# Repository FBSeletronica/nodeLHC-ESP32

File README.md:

## PT-BR

# nodeLHC-ESP32 

LIVE em formato Hands On Construindo o nova versão da placa de desenvolvimento nodeLHC ESP32, com o Pedro Minatel, utilizando a ferramenta Kicad, o módulo escolhido foi o ESP32 um microcontrolador de baixo custo da Espressif.

Em 2015 durante as oficinas de IoT no Hackerspace, criamos uma primeira versão do nodeLHC com o módulo ESP8266. Assim as pessoas aprenderam as diferentes etapas para construção de placa de circuitos impressos, também soldagem dos componentes da placa de desenvolvimento e programação para o módulo.

Descrições e detalhes:
Essa é uma primeira atividade que ao decorrer iremos construir novos projetos no formato aberto e colaborativo aproveitando a placa de desenvolvimento nodeLHC ESP32

- [KiCad](https://kicad-pcb.org/)
- [LHC KiCad Library](https://github.com/lhc/lhc_kicad_library)
- [Minatel KiCad Library](https://github.com/pedrominatel/minatel-kicad-libraries)
- [SparkFun KiCad Library](https://github.com/sparkfun/SparkFun-KiCad-Libraries)

# checklist
- [x] LIVE 1 - Explicação geral e desenho
- [x] LIVE 2 - Revisão esquemático e desenho da PCB parcial

# Próximos passos
- [ ] Lista de pessoas interessadas nos módulos
- [ ] Feedback comunidade
- [ ] LIVE 3 - Finalizar desenho da placa 
- [ ] Validar artes PCB
- [ ] Lista BOM
- [ ] Produção PCB

# Discourse 
Dúvidas? sugestões publicar na issues ou direto no discourse do LHC 

- [28/07/2020 LIVE - Hands On: Construindo o nodeLHC ESP32 com Kicad](https://discourse.lhc.net.br/t/28-07-2020-live-hands-on-construindo-o-nodelhc-esp32-com-kicad/148/2)
- [11/09/2020 LIVE - Hands On: Construindo o nodeLHC ESP32 com Kicad - Parte 02](https://discourse.lhc.net.br/t/11-09-2020-live-hands-on-construindo-o-nodelhc-esp32-com-kicad-parte-02/160)

# Ainda em construção 11/09/2020

# Log
- 19/08/2020 - Criado o evento, repositório, publicações nas redes sociais gerado link sobre a atividade.
- 02/09/2020 - Criado, divulgado o segundo evento, atualização de links no repositório.
- 06/10/2020 - Listagem das pessoas que responderam o discourse para receber o módulo ESP32

### Referencias

[ESP32 Datasheet](https://www.espressif.com/sites/default/files/documentation/esp32_datasheet_en.pdf)

[ESP32-WROOM Datasheet](https://www.espressif.com/sites/default/files/documentation/esp32-wroom-32d_esp32-wroom-32u_datasheet_en.pdf)

[ESP32 Design Guidelines](https://www.espressif.com/sites/default/files/documentation/esp32_hardware_design_guidelines_en.pdf)

[CH340G](https://cdn.sparkfun.com/datasheets/Dev/Arduino/Other/CH340DS1.PDF)

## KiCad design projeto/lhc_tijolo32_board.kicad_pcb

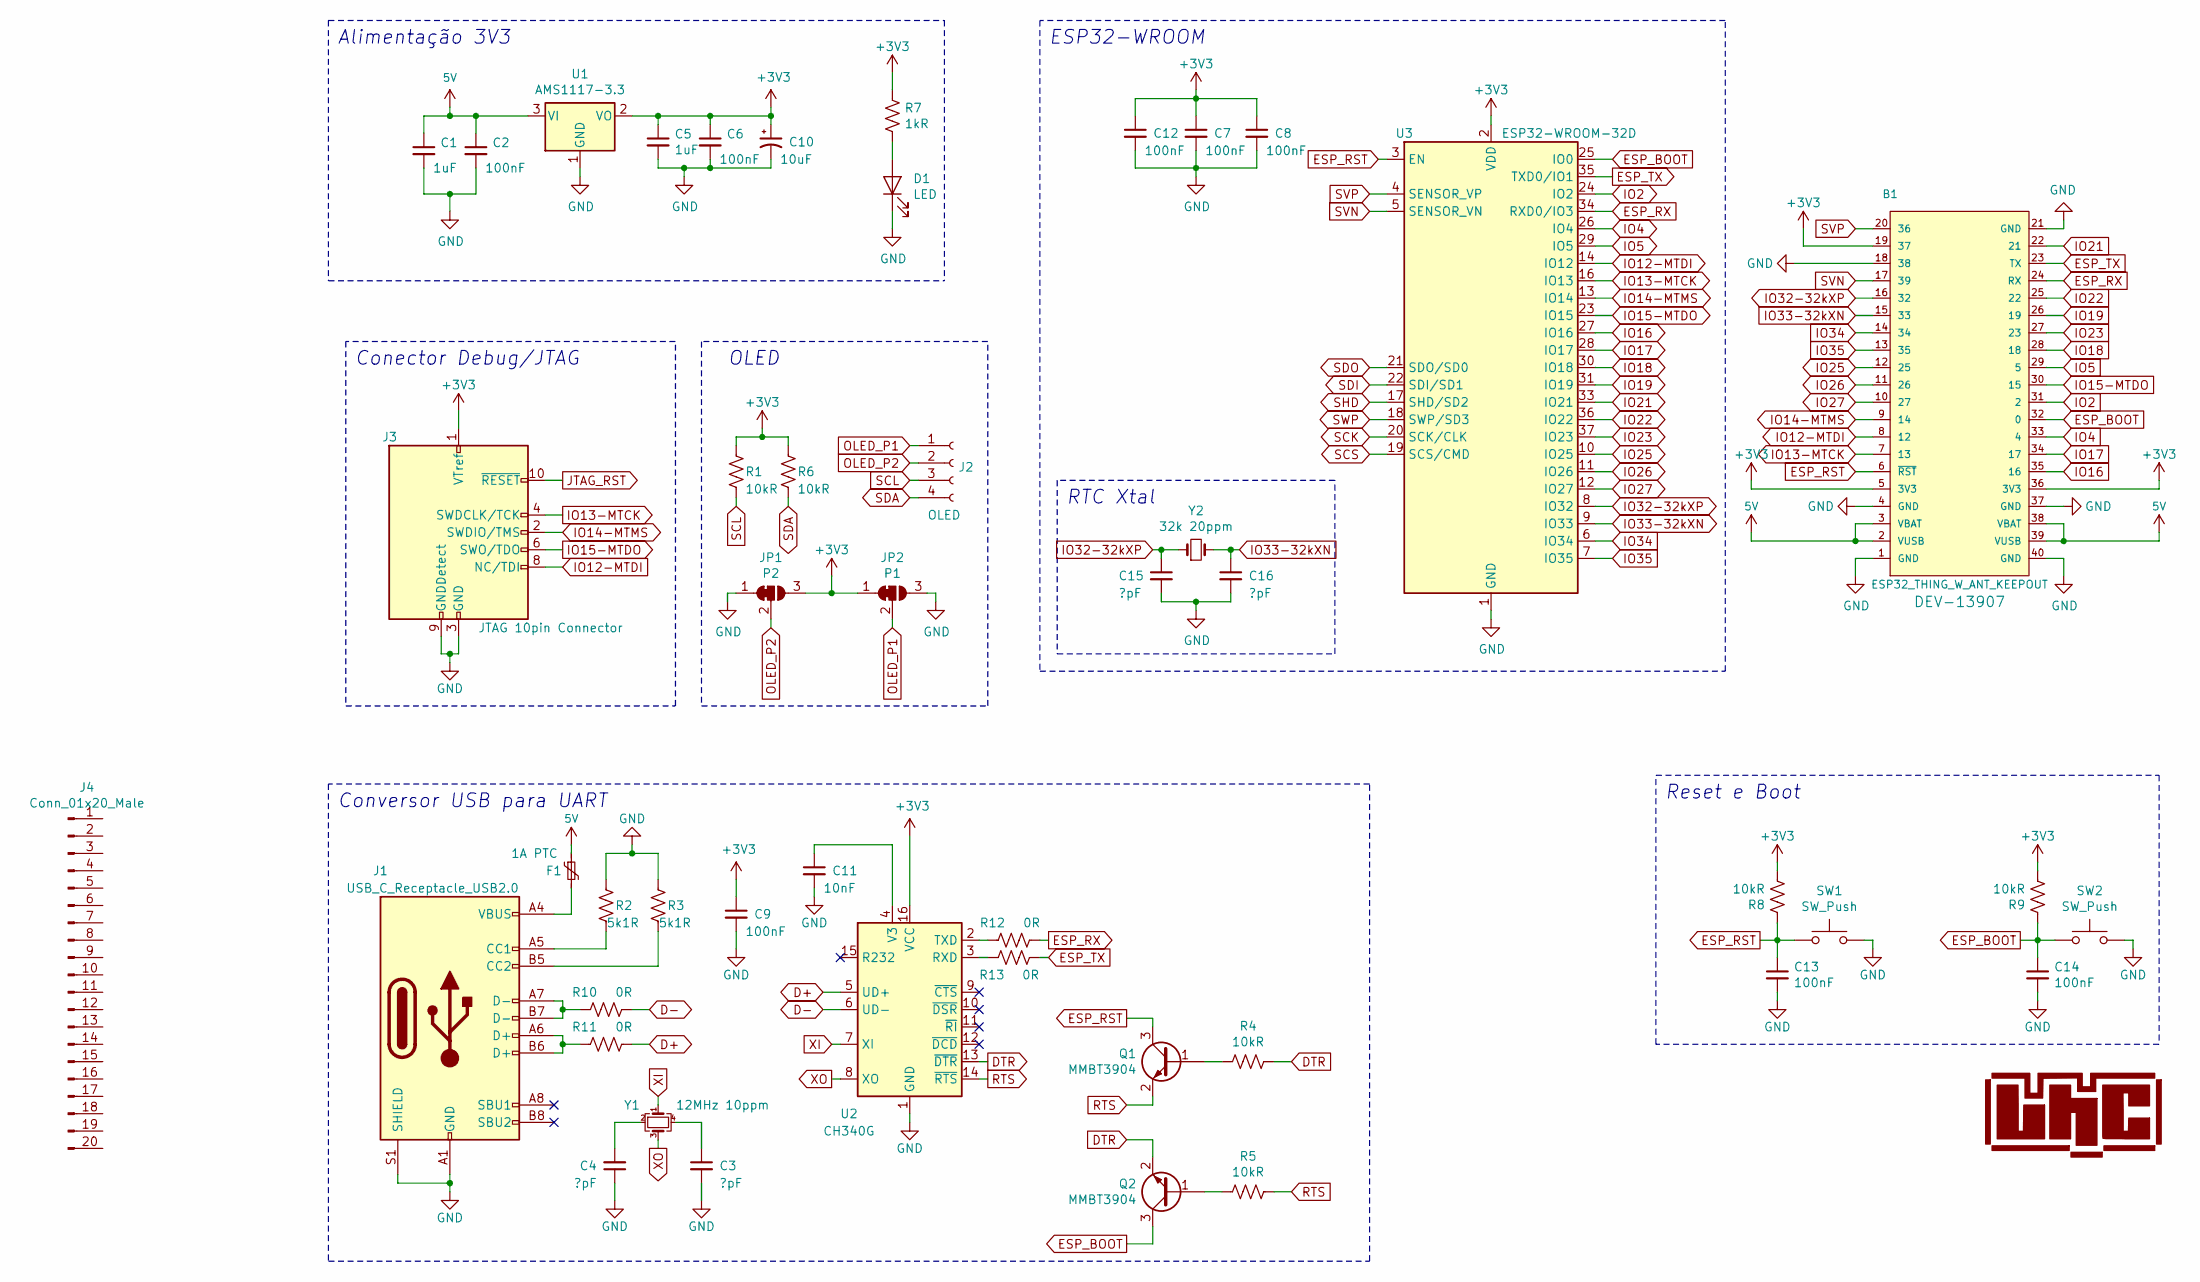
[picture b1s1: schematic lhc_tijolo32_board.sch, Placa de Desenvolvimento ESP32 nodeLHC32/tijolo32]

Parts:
B1: ESP32_THING_W_ANT_KEEPOUT; ESP32_THING
C1, C5: 1uF; C_0603_1608Metric
C2, C6, C7, C8, C9, C12, C13, C14: 100nF; C_0603_1608Metric
C3, C4, C15, C16: ?pF; C_0603_1608Metric
C10: 10uF; CP_EIA-3216-12_Kemet-S; LCSC C7171
C11: 10nF; C_0603_1608Metric
D1: LED; LED_0805_2012Metric
F1: 1A PTC; R_1210_3225Metric
J1: USB_C_Receptacle_USB2.0; USB_C_Receptacle_Palconn_UTC16-G
J2: OLED; PinHeader_1x04_P2.54mm_Vertical
J3: JTAG 10pin Connector; PinHeader_2x05_P1.27mm_Vertical_SMD
J4: Conn_01x20_Male; PinHeader_1x20_P2.54mm_Vertical
JP1: P2; SolderJumper-3_P1.3mm_Bridged12_Pad1.0x1.5mm_NumberLabels
JP2: P1; SolderJumper-3_P1.3mm_Bridged12_Pad1.0x1.5mm_NumberLabels
Q1, Q2: MMBT3904; SOT-23
R1, R4, R5, R6, R8, R9: 10kR; R_0603_1608Metric
R2, R3: 5k1R; R_0603_1608Metric
R7: 1kR; R_0603_1608Metric
R10, R11, R12, R13: 0R; R_0603_1608Metric
SW1, SW2: SW_Push; TACTILE_SWITCH_SMD_6.0X3.5MM
U1: AMS1117-3.3; SOT-223-3_TabPin2; LCSC C6186
U2: CH340G; SOIC-16_3.9x9.9mm_P1.27mm; MPN C14267
U3: ESP32-WROOM-32D; ESP32-WROOM-32
Y1: 12MHz 10ppm; Crystal_SMD_EuroQuartz_MT-4Pin_3.2x2.5mm
Y2: 32k 20ppm; Crystal_SMD_3215-2Pin_3.2x1.5mm

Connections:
5V: B1.2 (VUSB), B1.3 (VBAT), B1.38 (VBAT), B1.39 (VUSB), C1.1, C2.1, F1.1, U1.3 (VI)
+3V3: B1.5 (3V3), B1.19 (37), B1.36 (3V3), C5.1, C6.1, C7.1, C8.1, C9.1, C10.1, C12.1, J3.1 (VTref), JP1.3 (B), JP2.1 (A), R1.1, R6.1, R7.1, R8.2, R9.2, U1.2 (VO), U2.16 (VCC), U3.2 (VDD)
D+: R11.1, U2.5 (UD+)
D-: R10.1, U2.6 (UD-)
DTR: Q2.2 (E), R4.1, U2.13 (~DTR)
ESP_BOOT: B1.32 (0), C14.1, Q2.3 (C), R9.1, SW2.1, U3.25 (IO0)
ESP_RST: B1.6 (~RST~), C13.1, Q1.3 (C), R8.1, SW1.1, U3.3 (EN)
ESP_RX: B1.24 (RX), R12.1, U3.34 (RXD0/IO3)
ESP_TX: B1.23 (TX), R13.2, U3.35 (TXD0/IO1)
GND: B1.1 (GND), B1.4 (GND), B1.18 (38), B1.21 (GND), B1.37 (GND), B1.40 (GND), C1.2, C2.2, C3.2, C4.1, C5.2, C6.2, C7.2, C8.2, C9.2, C10.2, C11.2, C12.2, C13.2, C14.2, C15.2, C16.2, D1.1 (K), J1.A1 (GND), J1.A12 (GND), J1.B1 (GND), J1.B12 (GND), J1.S1 (SHIELD), J3.3 (GND), J3.5 (GND), J3.9 (GNDDetect), JP1.1 (A), JP2.3 (B), R2.1, R3.1, SW1.2, SW2.2, U1.1 (GND), U2.1 (GND), U3.1 (GND), U3.15 (GND), U3.38 (GND), U3.39 (GND)
IO2: B1.31 (2), U3.24 (IO2)
IO4: B1.33 (4), U3.26 (IO4)
IO5: B1.29 (5), U3.29 (IO5)
IO12-MTDI: B1.8 (12), J3.8 (NC/TDI), U3.14 (IO12)
IO13-MTCK: B1.7 (13), J3.4 (SWDCLK/TCK), U3.16 (IO13)
IO14-MTMS: B1.9 (14), J3.2 (SWDIO/TMS), U3.13 (IO14)
IO15-MTDO: B1.30 (15), J3.6 (SWO/TDO), U3.23 (IO15)
IO16: B1.35 (16), U3.27 (IO16)
IO17: B1.34 (17), U3.28 (IO17)
IO18: B1.28 (18), U3.30 (IO18)
IO19: B1.26 (19), U3.31 (IO19)
IO21: B1.22 (21), U3.33 (IO21)
IO22: B1.25 (22), U3.36 (IO22)
IO23: B1.27 (23), U3.37 (IO23)
IO25: B1.12 (25), U3.10 (IO25)
IO26: B1.11 (26), U3.11 (IO26)
IO27: B1.10 (27), U3.12 (IO27)
IO32-32kXP: B1.16 (32), C15.1, U3.8 (IO32), Y2.1
IO33-32kXN: B1.15 (33), C16.1, U3.9 (IO33), Y2.2
IO34: B1.14 (34), U3.6 (IO34)
IO35: B1.13 (35), U3.7 (IO35)
JTAG_RST: J3.10 (~RESET~)
unnamed: C3.1, Y1.4
unnamed: C4.2, Y1.2
unnamed: C11.1, U2.4 (V3)
unnamed: D1.2 (A), R7.2
unnamed: F1.2, J1.A4 (VBUS), J1.A9 (VBUS), J1.B4 (VBUS), J1.B9 (VBUS)
unnamed: J1.A5 (CC1), R2.2
unnamed: J1.A6 (D+), J1.B6 (D+), R11.2
unnamed: J1.A7 (D-), J1.B7 (D-), R10.2
unnamed: J1.B5 (CC2), R3.2
unnamed: Q1.1 (B), R4.2
unnamed: Q2.1 (B), R5.2
unnamed: R12.2, U2.2 (TXD)
unnamed: R13.1, U2.3 (RXD)
OLED_P1: J2.1, JP2.2 (C)
OLED_P2: J2.2, JP1.2 (C)
RTS: Q1.2 (E), R5.1, U2.14 (~RTS)
SCK: U3.20 (SCK/CLK)
SCL: J2.3, R1.2
SCS: U3.19 (SCS/CMD)
SDA: J2.4, R6.2
SDI: U3.22 (SDI/SD1)
SDO: U3.21 (SDO/SD0)
SHD: U3.17 (SHD/SD2)
SVN: B1.17 (39), U3.5 (SENSOR_VN)
SVP: B1.20 (36), U3.4 (SENSOR_VP)
SWP: U3.18 (SWP/SD3)
XI: U2.7 (XI), Y1.1
XO: U2.8 (XO), Y1.3

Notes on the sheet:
Alimentação 3V3
Conversor USB para UART
Conector Debug/JTAG
Reset e Boot
OLED
ESP32-WROOM
RTC Xtal

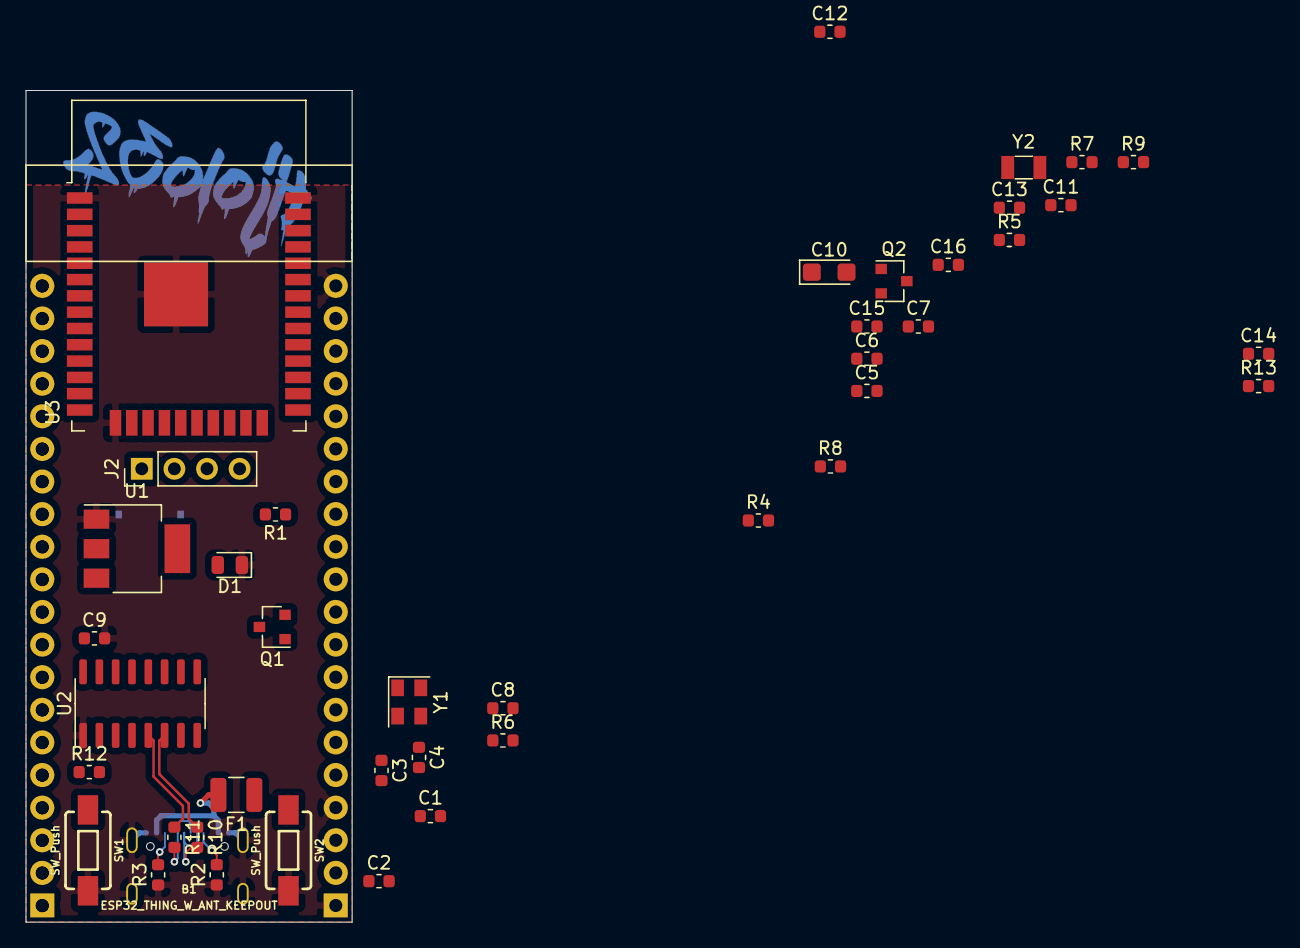
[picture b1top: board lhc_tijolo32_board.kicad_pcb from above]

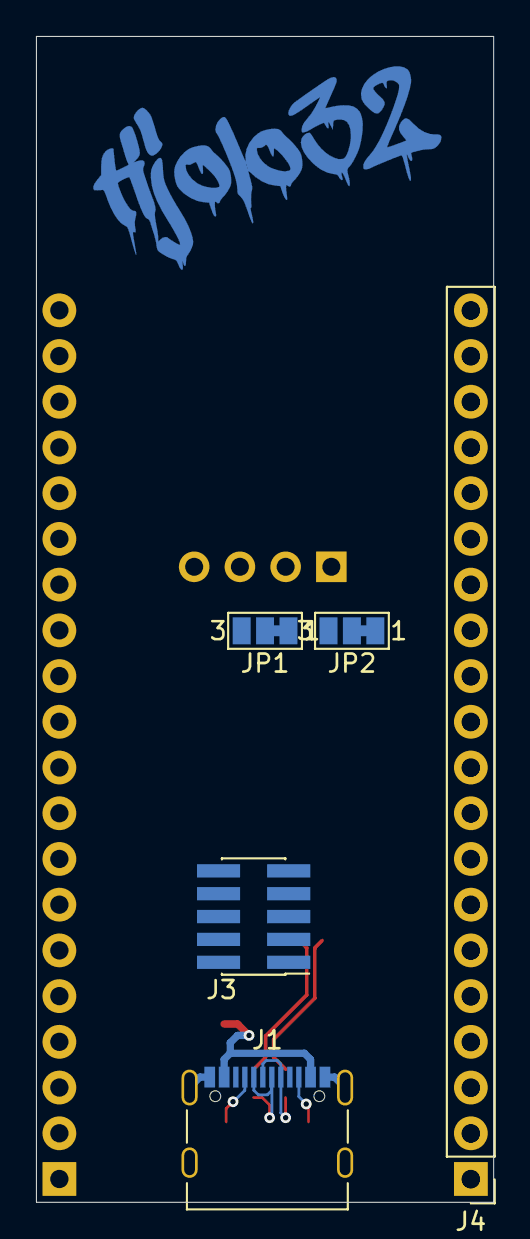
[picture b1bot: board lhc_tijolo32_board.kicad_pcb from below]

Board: 2 copper layers, 25.4 x 64.8 mm, 47 parts (5 on the bottom side), 53 nets.

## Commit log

2020-08-28 README updated with links
2020-08-29 Arquivos da live adicionados
2020-08-29 Conversor serial USB type C
2020-08-29 Troca do LDO para AMS1117-3-3
2020-08-29 Botão de reset/boot e conector OLED
2020-09-11 Sch WIP.Sync for live.
2020-09-11 Schematic update
